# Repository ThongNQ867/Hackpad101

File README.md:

# Hackpad101
I have went back and update this hackpad with these changes:
- Change to button matrix to enable more buttons 
- Include a rotary encoder
- Include 4 pins for an 0.91' OLED screen
Because of that, the case is also updated.
Here is the schematic:

Here is the PCB: 

Here is the case: 

BOM:
- XIAO RP2040 DIP
- 2 RGB SK6812 MINI
- 5 Cherry MX switches
- 5 Blank DSA Keycaps
- 3-D printed case (2 parts)
- 1 EC11 rotary encoder
- 1 I2C 0.91' OLED

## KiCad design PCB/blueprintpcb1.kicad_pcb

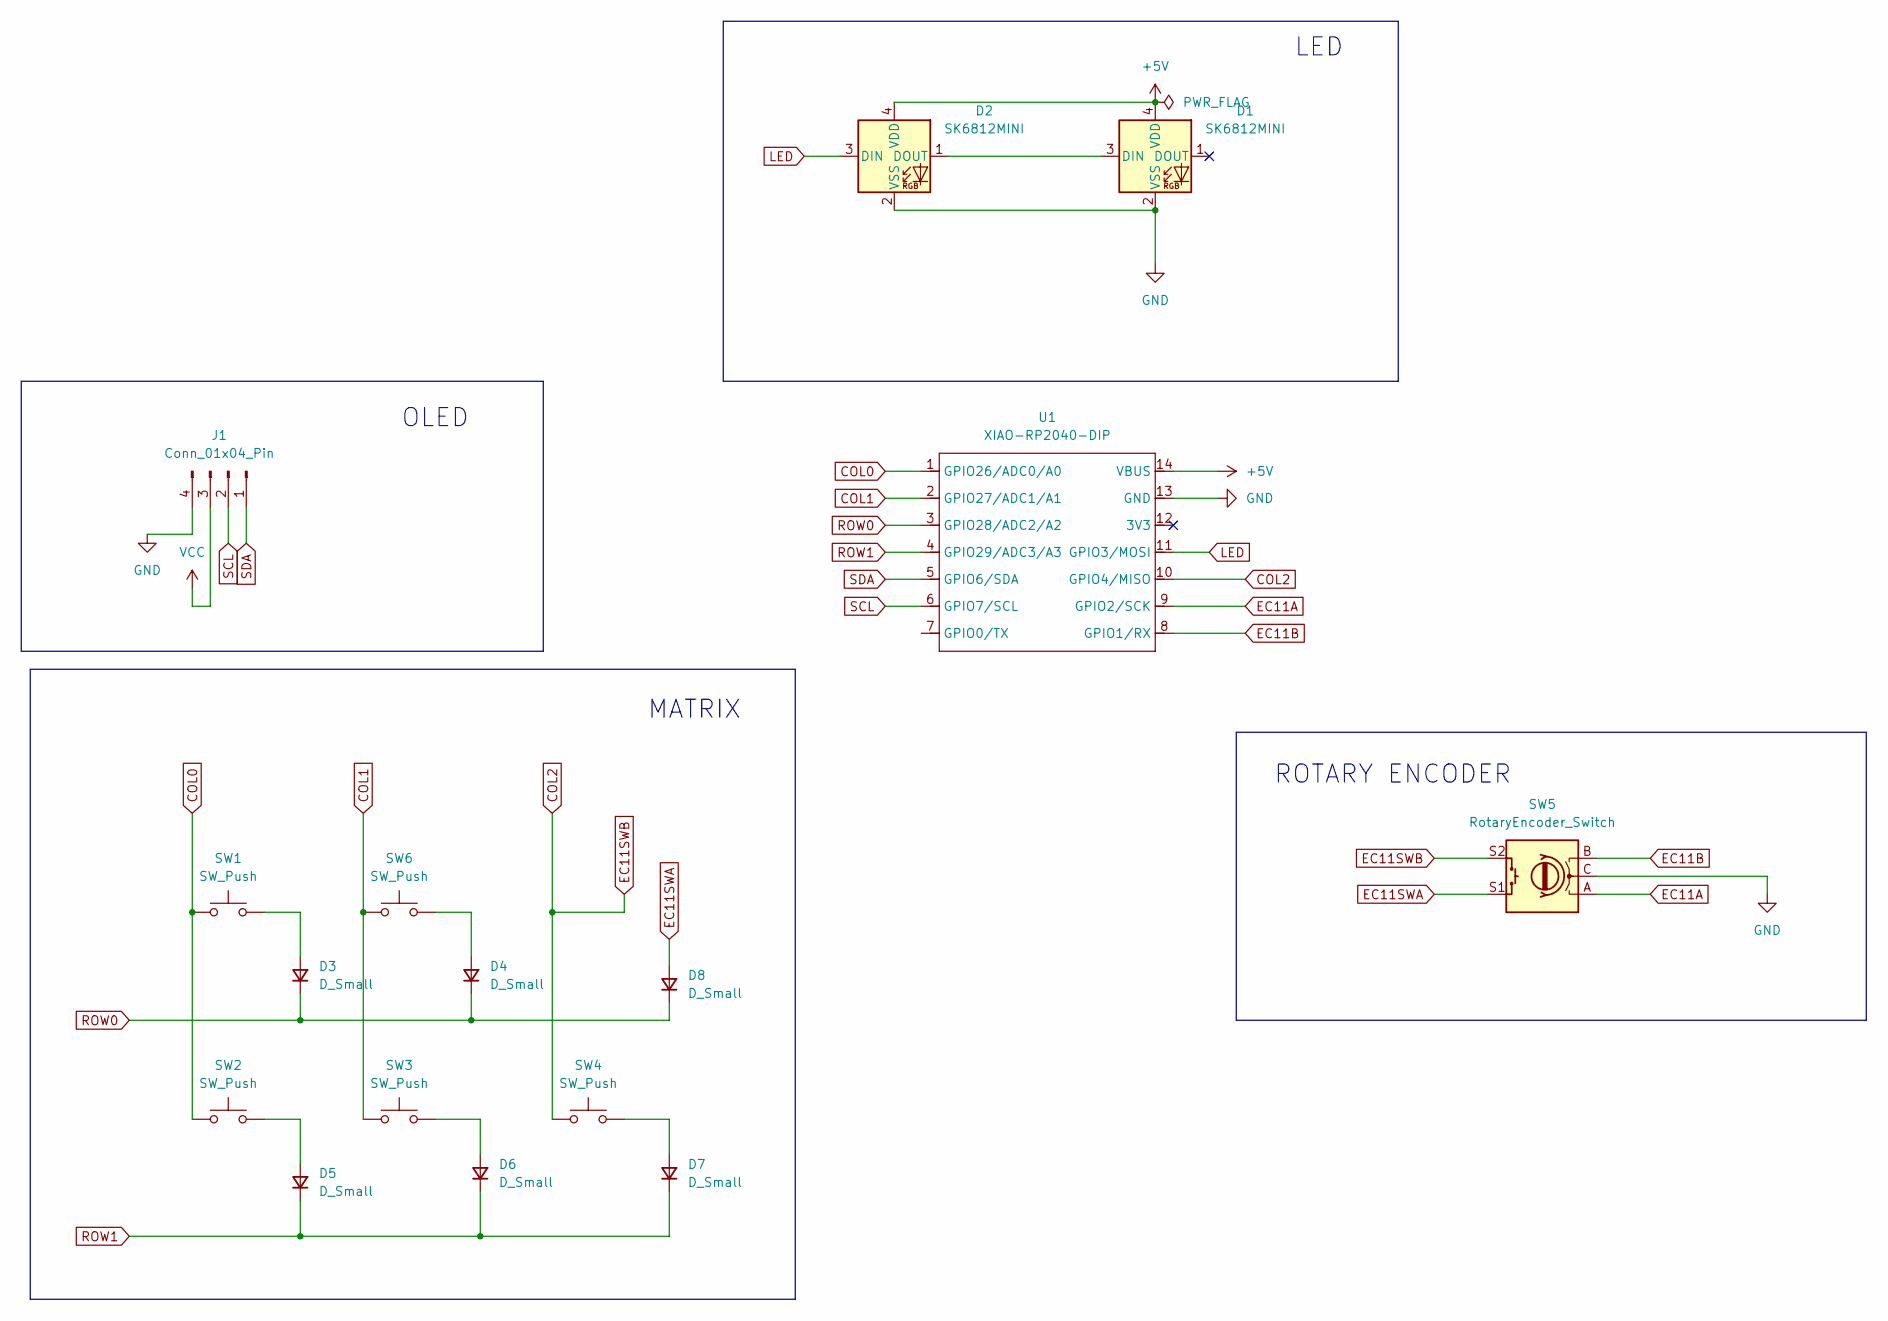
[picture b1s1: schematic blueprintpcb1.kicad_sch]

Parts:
D1, D2: SK6812MINI; MX_SK6812MINI-E_REV
D3, D4, D5, D6, D7, D8: D_Small; D_DO-35_SOD27_P7.62mm_Horizontal
J1: Conn_01x04_Pin; PinHeader_1x04_P2.54mm_Vertical
SW1, SW2, SW3, SW4, SW6: SW_Push; SW_Cherry_MX_1.00u_PCB
SW5: RotaryEncoder_Switch; RotaryEncoder_Alps_EC11E-Switch_Vertical_H20mm
U1: XIAO-RP2040-DIP

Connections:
+5V: D1.4 (VDD), D2.4 (VDD), U1.14 (VBUS)
COL0: SW1.1, SW2.1, U1.1 (GPIO26/ADC0/A0)
COL1: SW3.1, SW6.1, U1.2 (GPIO27/ADC1/A1)
COL2: SW4.1, SW5.S2, U1.10 (GPIO4/MISO)
EC11A: SW5.A, U1.9 (GPIO2/SCK)
EC11B: SW5.B, U1.8 (GPIO1/RX)
EC11SWA: D8.2 (A), SW5.S1
GND: D1.2 (VSS), D2.2 (VSS), J1.4, SW5.C, U1.13 (GND)
LED: D2.3 (DIN), U1.11 (GPIO3/MOSI)
unnamed: D1.3 (DIN), D2.1 (DOUT)
unnamed: D3.2 (A), SW1.2
unnamed: D4.2 (A), SW6.2
unnamed: D5.2 (A), SW2.2
unnamed: D6.2 (A), SW3.2
unnamed: D7.2 (A), SW4.2
ROW0: D3.1 (K), D4.1 (K), D8.1 (K), U1.3 (GPIO28/ADC2/A2)
ROW1: D5.1 (K), D6.1 (K), D7.1 (K), U1.4 (GPIO29/ADC3/A3)
SCL: J1.2, U1.6 (GPIO7/SCL)
SDA: J1.1, U1.5 (GPIO6/SDA)
VCC: J1.3

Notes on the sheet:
ROTARY ENCODER
OLED
MATRIX
LED

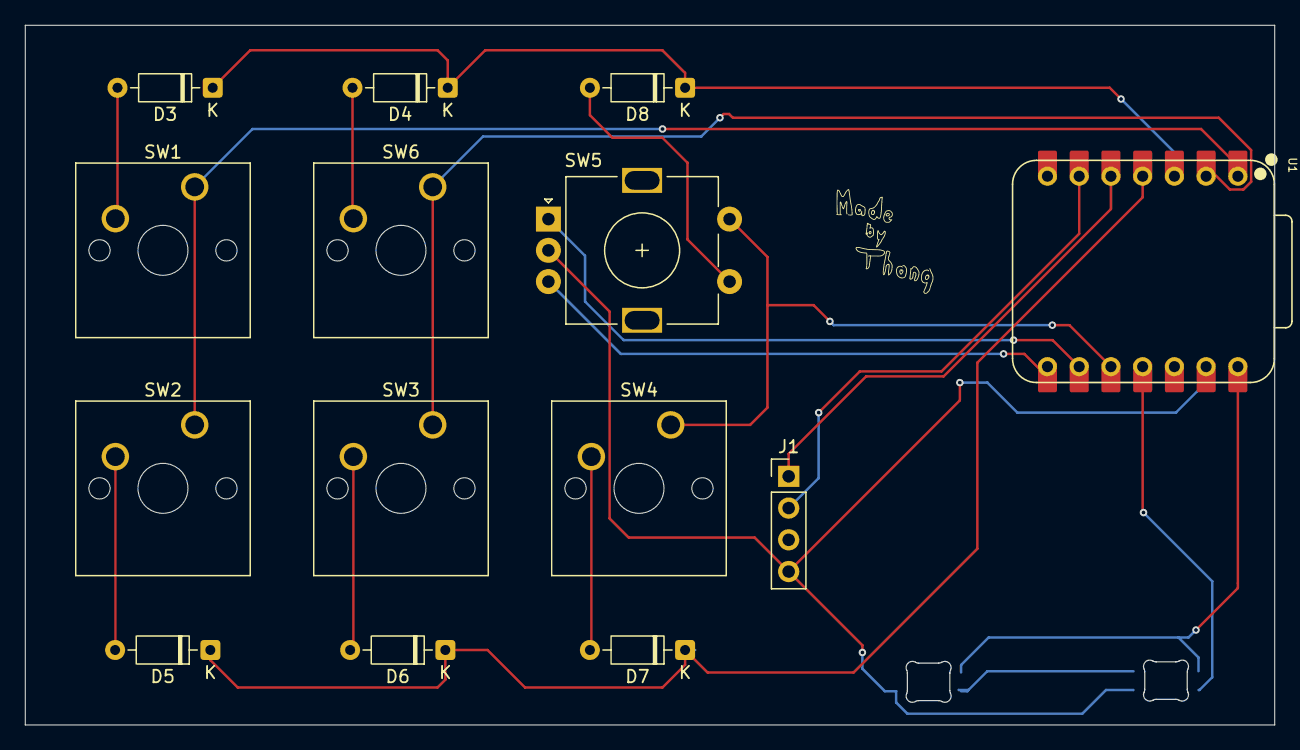
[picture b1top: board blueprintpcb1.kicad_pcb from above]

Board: 2 copper layers, 99.9 x 56.0 mm, 16 parts (0 on the bottom side), 19 nets.

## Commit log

2026-01-12 Add README
2026-01-31 ver2
2026-01-31 Hackpadv2
    Updated README to reflect changes in Hackpad101, including new features and images.
2026-01-31 ver2 cad file
2026-02-02 update pcb
